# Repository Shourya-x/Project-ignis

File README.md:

# Project IGNIS — STM32G473VET6 Rocket Flight Computer & Active Fin / TVC Avionics Suite

[-03234B?style=flat-square)](IGNIS_CORE/Firmware/HAL%20STM32/IGNIS_CORE_STM32G473VET6)

> **Open-source high-power model rocket flight computer, 4-channel X-configuration active fin / TVC attitude controller, 3-stage high-current MOSFET pyro igniter system, dual-EEPROM blackbox recorder, and 433 MHz LoRa telemetry ground station.**

---

## 1. Executive Summary

**Project IGNIS** is a vertically integrated aerospace avionics and mechanical control platform engineered from custom bare-metal `STM32G473VET6` HAL firmware and 2-layer KiCad PCBs to a parametric FreeCAD airframe and a PyQt6/OpenGL ground station.

Unlike hobby flight controllers built around legacy `STM32F4` drone boards, **IGNIS-CORE** is purpose-built around the **`STM32G473VET6`** (LQFP-100, 170 MHz ARM Cortex-M4F with hardware **CORDIC** trigonometric and **FMAC** filter co-processors, 512 KB ECC Flash, 128 KB SRAM, 6 internal PGA op-amps, and 7 ultra-fast 16 ns comparators).

### Key Subsystem Capabilities

| Subsystem | Hardware Implementation | Key Specifications |
| :--- | :--- | :--- |
| **Flight Computer (`IGNIS_CORE`)** | Custom KiCad PCB + **`STM32G473VET6`** (LQFP-100) | 144 MHz PLL (`8 MHz` HSE `X1` + `32.768 kHz` LSE `X2`), 512 KB ECC Flash, 128 KB SRAM |
| **Inertial & Barometric Suite (`I2C2`)** | **`MPU-6500`** (`0x68`) + **`MS5611-01BA03`** (`0x77`) + **`HMC5883L` / `BMM150`** (`0x1E`) | $\pm 8\text{g}$ Accel ($4096\text{ LSB/g}$), $\pm 1000^\circ/\text{s}$ Gyro ($32.8\text{ LSB}/^\circ/\text{s}$), 24-bit $\Delta\Sigma$ Baro ($\text{OSR}=4096$, $\sim 10\text{ cm}$ resolution) |
| **Attitude & X-Fin / TVC Actuation** | 4× High-Speed Digital Servos on **`TIM2_CH1..4`** (`PA0–PA3`) | `100 Hz` Complementary Filter ($\alpha=0.98$) + 3-Axis PID ($K_p=1.2, K_i=0.05, K_d=0.08$) + 4-Fin X-Mixing |
| **3-Channel Pyro Igniter Stage** | 2× **`IRLZ44N`** (`PC7`, `PC8`) + 1× **`IRF520`** w/ Dual-`BC547` Level Shifter (`PC9`) | Motor Ignition (`PC7`), Stage Separation (`PC8`), Parachute Ejection (`PC9`) with `1N4007` flyback clamp diodes |
| **Telemetry & Navigation** | **`Ai-Thinker Ra-02 (SX1278)`** (`SPI1`) + **`u-blox NEO-7M`** (`USART1`) | 433 MHz LoRa long-range link (`>5 km` LOS), contiguous LQFP-100 pin routing (`Pins 90–95`) + 10 Hz GPS |
| **Dual-Tier Flight Storage** | Onboard **`24LC16B`** EEPROM (`0x50–0x57`) + **`microSD`** (`SPI2`) + **`Aux Data Logger PCB`** | Hot-start state & calibration recovery + `ATmega328P` / Dual `24LC1025` (256 KB) / `DS1337S+` RTC blackbox |
| **Diagnostics & Ground Interface** | **`WS2812B`** DMA Engine (`PB9`) + 5V NPN Buzzer (`PC6`) + **`USB-C CDC`** (`PA11/PA12`) | Zero-CPU `TIM4_CH4` + `DMA1_Channel1` 800 kHz NeoPixel driver + 100 Hz CSV telemetry stream & CLI |

---

## 2. System Architecture

```
┌─────────────────────────────────────────────────────────────────────────────────────────────────┐
│                                  PROJECT IGNIS AVIONICS STACK                                   │
├─────────────────────────────────────────────────────────────────────────────────────────────────┤
│                                                                                                 │
│  ┌───────────────────────────────────────┐        ┌──────────────────────────────────────────┐  │
│  │        I2C2 SENSOR & NVM BUS          │        │        TELEMETRY, GPS & STORAGE          │  │
│  │        (SCL = PC4, SDA = PA8)         │        │                                          │  │
│  │  • MPU-6500 6-Axis IMU       [0x68]   │        │  • SX1278 Ra-02 LoRa (SPI1: PB3–PB8)     │  │
│  │  • MS5611-01BA03 Barometer   [0x77]   │        │  • u-blox NEO-7M GPS (USART1: PA9/PA10)  │  │
│  │  • HMC5883L / BMM150 Mag     [0x1E]   │        │  • microSD Slot      (SPI2: PB12–PB15)   │  │
│  │  • 24LC16B Hot-Start EEPROM  [0x50]   │        │  • USB-C Full-Speed  (CDC: PA11/PA12)    │  │
│  └──────────────────┬────────────────────┘        └────────────────────┬─────────────────────┘  │
│                     │                                                  │                        │
│                     ▼                                                  ▼                        │
│  ┌───────────────────────────────────────────────────────────────────────────────────────────┐  │
│  │                        IGNIS-CORE FLIGHT COMPUTER (STM32G473VET6)                         │  │
│  │            170 MHz Cortex-M4F (144 MHz PLL) • CORDIC + FMAC • 512 KB ECC Flash            │  │
│  │     100 Hz Attitude Loop: Complementary Filter (α=0.98) ──► 3-Axis PID ──► X-Fin Mixer    │  │
│  └──────────────────┬──────────────────────────────────────────────────┬─────────────────────┘  │
│                     │                                                  │                        │
│                     ▼ TIM2 50Hz PWM (PA0–PA3)                          ▼ High-Current Switching │
│  ┌───────────────────────────────────────┐        ┌──────────────────────────────────────────┐  │
│  │     IGNIS-CTRL ACTUATION STAGE        │        │      3-CHANNEL PYRO & DIAGNOSTICS        │  │
│  │  • Fin 1 (45°  / Q1: +X,+Y) : PA0 (CH1)│       │  • PC7 (PYRO_MOTOR) : IRLZ44N Logic FET  │  │
│  │  • Fin 2 (135° / Q2: -X,+Y) : PA1 (CH2)│       │  • PC8 (PYRO_SEP)   : IRLZ44N Logic FET  │  │
│  │  • Fin 3 (225° / Q3: -X,-Y) : PA2 (CH3)│       │  • PC9 (PYRO_CHUTE) : 2x BC547 + IRF520  │  │
│  │  • Fin 4 (315° / Q4: +X,-Y) : PA3 (CH4)│       │  • PC6 (BUZZER)     : BC547 + 1N4007     │  │
│  │  • 2-Axis TVC Gimbal Assembly         │        │  • PB9 (WS2812B)    : TIM4_CH4 + DMA     │  │
│  └───────────────────────────────────────┘        └──────────────────────────────────────────┘  │
│                                                                                                 │
└─────────────────────────────────────────────────────────────────────────────────────────────────┘
```

---

## 3. Repository Structure

```text
Project-ignis/
├── IGNIS_CORE/
│   ├── Firmware/
│   │   ├── HAL STM32/IGNIS_CORE_STM32G473VET6/  # Primary STM32CubeMX + CMake + Modular HAL Firmware
│   │   │   ├── Core/                            # CubeMX-generated peripheral init (gpio, dma, i2c, spi, tim, usart)
│   │   │   ├── Modules/                         # 11 CubeMX-safe hardware & GNC modules:
│   │   │   │   ├── Flight/                      # 100 Hz Complementary filter, 3-axis PID & X-fin mixing
│   │   │   │   ├── IMU/                         # MPU-6500 register driver & 500-sample offset calibration
│   │   │   │   ├── Barometer/                   # MS5611 PROM C1-C6 reader & 2nd-order temp-compensated ADC
│   │   │   │   ├── Sensors/                     # I2C2 bus scanner (0x08-0x77) & HMC5883L 3-axis magnetometer
│   │   │   │   ├── Servos/                      # TIM2 4-channel 50 Hz hardware PWM (1000-2000 µs)
│   │   │   │   ├── WS2812/                      # TIM4_CH4 + DMA1_Channel1 zero-CPU NeoPixel pulse engine
│   │   │   │   ├── EEPROM/                      # 24LC16B 8-block (0x50-0x57) hot-start & calibration storage
│   │   │   │   ├── LoRa/                        # SX1278 (Ra-02) SPI1 radio driver
│   │   │   │   ├── GPS/                         # u-blox NEO-7M USART1 NMEA parser
│   │   │   │   ├── Logger/ & Storage/           # SPI2 microSD & blackbox telemetry logging
│   │   │   │   └── USB/                         # USB-C Full-Speed CDC 100 Hz CSV stream & interactive CLI
│   │   │   ├── IGNIS_CORE_STM32G473VET6.ioc     # STM32CubeMX hardware pinout & clock definition
│   │   │   ├── CMakeLists.txt                   # CMake + Ninja build definition
│   │   │   └── new_module.sh                    # Automated HAL module generator script
│   │   └── PlatFormio/                          # Legacy prototype firmware archive
│   ├── Hardware/
│   │   ├── Project_IGNIS_CORE/                  # Main Flight Computer KiCad 9/10 Schematic, PCB & STEP
│   │   ├── 3D_Models/ & Footprints.pretty/      # Custom SMD/THT footprints & 3D component models
│   │   └── Documentation/                       # Exported schematics.pdf & BOM.xlsx
│   └── Aux Hardware/Data Logger/data logger/    # Standalone ATmega328P + 2x 24LC1025 + DS1337S RTC PCB
│
├── IGNIS_CTRL/
│   └── Mechanical_Design/                       # TVC gimbal STEP/STL CAD files (thrust plate, linkages, mounts)
│
├── IGNIS_NET/
│   ├── IGNIS-NET-SIM/                           # PyQt6 + PyQtGraph + PyOpenGL Ground Station & Flight Replayer
│   ├── Firmware/                                # Ground station receiver firmware
│   └── Documentation/                           # Ground station user manual & API docs
│
├── Rocket_Assembly/
│   ├── Airframe And Parts/                      # Parametric FreeCAD (.FCStd), STEP & STL rocket body, fins, nosecone
│   ├── Avionics_Bay/                            # Modular avionics bay (.FCStd, .gltf, .stl), shock mounts & core mount
│   └── Full_Assembly/                           # Complete rocket assembly & cutaway STEP models
│
├── Documentation/                               # Comprehensive engineering & hardware documentation
│   ├── System_Overview.md                       # Architecture, G4 vs F4 trade study, control loop & power tree
│   ├── Wiring_Guide.md                          # Complete LQFP-100 pinout, Pyro MOSFET & Buzzer schematics
│   ├── Communication_Protocol.md                # USB CDC 100 Hz CSV, CLI commands & LoRa telemetry frame specs
│   ├── Calibration_Guide.md                     # IMU 500-sample bias, MS5611 PROM, Magnetometer & Servo centering
│   └── Troubleshooting.md                       # Hardware bringup, WS2812 DMA timing, I2C2 mux & PCB DRC notes
│
└── ignis-website/                               # Astro Technical Datasheet & 3D Interactive Avionics Showcase
```

---

## 4. Complete `STM32G473VET6` (LQFP-100) Pinout Matrix

| LQFP-100 Pin | GPIO Pin | Peripheral / Mode | Signal Label | Connected Hardware & Engineering Notes |
| :---: | :---: | :--- | :--- | :--- |
| **Pin 12 / 13** | `PH0 / PH1` | `RCC_OSC_IN / OUT` | `HSE_8MHZ` | `X1` 8.000 MHz HC-49US crystal $\rightarrow$ PLL $\times 36 / 2 = \mathbf{144\text{ MHz}}$ `SYSCLK` |
| **Pin 8 / 9** | `PC14 / PC15` | `RCC_OSC32_IN / OUT` | `LSE_32K` | `X2` 32.768 kHz RTC crystal |
| **Pin 30** | **`PC4`** | `I2C2_SCL` (AF4) | `I2C2_SCL` | `MPU-6500` (`0x68`), `MS5611` (`0x77`), `HMC5883L` (`0x1E`), `24LC16B` (`0x50–0x57`) |
| **Pin 69** | **`PA8`** | `I2C2_SDA` (AF4) | `I2C2_SDA` | Shared `I2C2` bus (`4.7 kΩ` pull-ups to `+3.3V`) |
| **Pin 22** | **`PA0`** | `TIM2_CH1` (AF1) | `SERVO_FIN1` | **Fin 1 (45° / Q1: +X, +Y)** 50 Hz PWM (`1000–2000 µs`, $90^\circ = 1500\,\mu\text{s}$) |
| **Pin 23** | **`PA1`** | `TIM2_CH2` (AF1) | `SERVO_FIN2` | **Fin 2 (135° / Q2: -X, +Y)** 50 Hz PWM (`1000–2000 µs`) |
| **Pin 24** | **`PA2`** | `TIM2_CH3` (AF1) | `SERVO_FIN3` | **Fin 3 (225° / Q3: -X, -Y)** 50 Hz PWM (`1000–2000 µs`) |
| **Pin 25** | **`PA3`** | `TIM2_CH4` (AF1) | `SERVO_FIN4` | **Fin 4 (315° / Q4: +X, -Y)** 50 Hz PWM (`1000–2000 µs`) |
| **Pin 90** | **`PB3`** | `SPI1_SCK` (AF5) | `LORA_SCK` | `Ai-Thinker Ra-02 (SX1278)` Clock (Consecutive LQFP row `Pins 90–95`) |
| **Pin 91** | **`PB4`** | `SPI1_MISO` (AF5) | `LORA_MISO` | `Ai-Thinker Ra-02 (SX1278)` MISO |
| **Pin 92** | **`PB5`** | `SPI1_MOSI` (AF5) | `LORA_MOSI` | `Ai-Thinker Ra-02 (SX1278)` MOSI |
| **Pin 93** | **`PB6`** | `GPIO_Output` | `LORA_RST` | `Ai-Thinker Ra-02 (SX1278)` Active-Low Reset (Default `HIGH`) |
| **Pin 94** | **`PB7`** | `GPIO_Output` | `LORA_CS` | `Ai-Thinker Ra-02 (SX1278)` Chip Select (`NSS`, Default `HIGH`) |
| **Pin 95** | **`PB8`** | `GPIO_EXTI8` | `LORA_DIO0` | `Ai-Thinker Ra-02 (SX1278)` Packet Tx/Rx Done Interrupt |
| **Pin 96** | **`PB9`** | `TIM4_CH4` + `DMA1_CH1` | `WS2812_DI` | `WS2812B` Addressable Status LED (`800 kHz`, 2 preamble + 24 data + 240 reset slots) |
| **Pin 70** | **`PA9`** | `USART1_TX` (AF7) | `GPS_RXD` | `u-blox NEO-7M` GPS Receiver (`9600` baud) |
| **Pin 71** | **`PA10`** | `USART1_RX` (AF7) | `GPS_TXD` | `u-blox NEO-7M` GPS Transmitter (`9600` baud) |
| **Pin 51** | **`PB12`** | `GPIO_Output` | `SD_CS` | `microSD` Card SPI Chip Select (Default `HIGH`) |
| **Pin 52** | **`PB13`** | `SPI2_SCK` (AF5) | `SD_SCK` | `microSD` Card SPI2 Clock |
| **Pin 53** | **`PB14`** | `SPI2_MISO` (AF5) | `SD_MISO` | `microSD` Card SPI2 MISO |
| **Pin 54** | **`PB15`** | `SPI2_MOSI` (AF5) | `SD_MOSI` | `microSD` Card SPI2 MOSI |
| **Pin 65** | **`PC6`** | `GPIO_Output` | `BUZZER` | 5V Piezo Buzzer via `BC547` NPN low-side driver + `1N4007` flyback diode |
| **Pin 66** | **`PC7`** | `GPIO_Output` | `PYRO_MOTOR` | **Pyro Channel 1 (Motor Igniter)** — Direct 3.3V logic gate drive to `IRLZ44N` |
| **Pin 67** | **`PC8`** | `GPIO_Output` | `PYRO_SEP` | **Pyro Channel 2 (Stage Separation)** — Direct 3.3V logic gate drive to `IRLZ44N` |
| **Pin 68** | **`PC9`** | `GPIO_Output` | `PYRO_CHUTE` | **Pyro Channel 3 (Parachute Ejection)** — Dual-`BC547` NPN level-shifter $\rightarrow$ `IRF520` (`V_GS = V_BAT`) |
| **Pin 72 / 73** | **`PA11 / PA12`** | `USB_DM / USB_DP` | `USB_CDC` | USB-C Full-Speed Virtual COM Port (`100 Hz` telemetry & interactive command console) |
| **Pin 76 / 79** | **`PA13 / PA14`** | `SYS_JTMS / JTCK` | `SWDIO / SWCLK` | ST-Link V2 Serial Wire Debug & Flash Programming |

---

## 5. Flight Control Loop & X-Configuration Fin Mixing

The attitude control loop in [`Flight.c`](IGNIS_CORE/Firmware/HAL%20STM32/IGNIS_CORE_STM32G473VET6/Modules/Flight/Flight.c) executes deterministically at **`100 Hz` ($\Delta t = 10\text{ ms}$)**:

1. **Inertial Attitude Estimation (Complementary Filter, $\alpha = 0.98$)**:
   $$\theta_{\text{accel}} = \text{atan2}\!\left(-a_x, \sqrt{a_y^2 + a_z^2}\right)\cdot\frac{180}{\pi}, \qquad \phi_{\text{accel}} = \text{atan2}\!\left(a_y, -a_z\right)\cdot\frac{180}{\pi}$$
   $$\theta_k = 0.98\left(\theta_{k-1} + \omega_x \Delta t\right) + 0.02\,\theta_{\text{accel}}, \qquad \phi_k = 0.98\left(\phi_{k-1} + \omega_y \Delta t\right) + 0.02\,\phi_{\text{accel}}$$

2. **3-Axis PID Attitude Controller** ($K_p = 1.20$, $K_i = 0.05$, $K_d = 0.08$, anti-windup clamped to $\pm 100^\circ$):
   - Pitch & Roll hold vertical attitude setpoint ($0.0^\circ$); Yaw damps angular rate ($\omega_z \rightarrow 0^\circ/\text{s}$).

3. **Orthogonal 4-Fin X-Configuration Aerodynamic Mixing Matrix**:
   $$\begin{bmatrix} \delta_1\ (45^\circ\text{ / Q1}) \\ \delta_2\ (135^\circ\text{ / Q2}) \\ \delta_3\ (225^\circ\text{ / Q3}) \\ \delta_4\ (315^\circ\text{ / Q4}) \end{bmatrix} = 90^\circ + \begin{bmatrix} -0.707 & +1.0 & -0.707 \\ +0.707 & +1.0 & -0.707 \\ +0.707 & +1.0 & +0.707 \\ -0.707 & +1.0 & +0.707 \end{bmatrix} \begin{bmatrix} u_{\text{pitch}} \\ u_{\text{roll}} \\ u_{\text{yaw}} \end{bmatrix}, \quad \delta_i \in [0^\circ, 180^\circ]$$

---

## 6. Quick Start — Firmware, Simulator & Website

### A. Build & Flash `IGNIS_CORE` (`STM32G473VET6`)

```bash
cd "IGNIS_CORE/Firmware/HAL STM32/IGNIS_CORE_STM32G473VET6"
cmake --preset Debug
cmake --build build/Debug -j

# Flash via ST-Link over SWD:
STM32_Programmer_CLI -c port=SWD -w build/Debug/IGNIS_CORE_STM32G473VET6.elf -v -rst
```

### B. Launch the `IGNIS-NET-SIM` Ground Station & Post-Flight Analyzer

```bash
cd IGNIS_NET/IGNIS-NET-SIM
python3 -m venv venv
source venv/bin/activate
pip install -r requirements.txt
python3 src/main.py
```

### C. Run the Technical Datasheet & 3D Avionics Website

```bash
cd ignis-website
npm install
npm run dev      # Local dev server at http://localhost:4321
npm run build    # Static bundle output into ./dist/
```

---

## 7. Engineering Documentation Index

- **[System Overview & Architecture](Documentation/System_Overview.md)** — `STM32G473VET6` vs `STM32F4` trade study, power regulation architecture, state machine, and Aux Blackbox Data Logger design.
- **[Hardware Wiring & Circuit Guide](Documentation/Wiring_Guide.md)** — Pin-by-pin LQFP-100 connections, `IRLZ44N` & `2× BC547 + IRF520` Pyro Igniter schematics, `5V` Buzzer driver, and `24LC16B` wiring.
- **[Communication & Telemetry Protocol](Documentation/Communication_Protocol.md)** — `100 Hz` USB CDC CSV format, single-character CLI commands (`A`, `D`, `C`, `S`), and `SX1278` LoRa telemetry frames.
- **[Sensor & Actuator Calibration Guide](Documentation/Calibration_Guide.md)** — 500-sample IMU bias calibration, `MS5611` 2nd-order PROM compensation, `HMC5883L` heading calibration, and fin trim alignment.
- **[Hardware Bringup & Troubleshooting](Documentation/Troubleshooting.md)** — `WS2812B` `TIM4_CH4` DMA waveform verification, `I2C2` `PC4`/`PA8` pin mux notes, and `IGNIS_CORE` PCB rev-1 ERC/DRC audit checklist.

---

## 8. License

- **Firmware, Ground Station Software & Documentation**: Licensed under the **MIT License**.
- **Hardware Schematics, PCB Layouts & Mechanical CAD**: Released under the **CERN Open Hardware Licence v2 — Permissive (CERN-OHL-P v2)**.

---
*Designed and engineered by **Shourya Pandey**.*

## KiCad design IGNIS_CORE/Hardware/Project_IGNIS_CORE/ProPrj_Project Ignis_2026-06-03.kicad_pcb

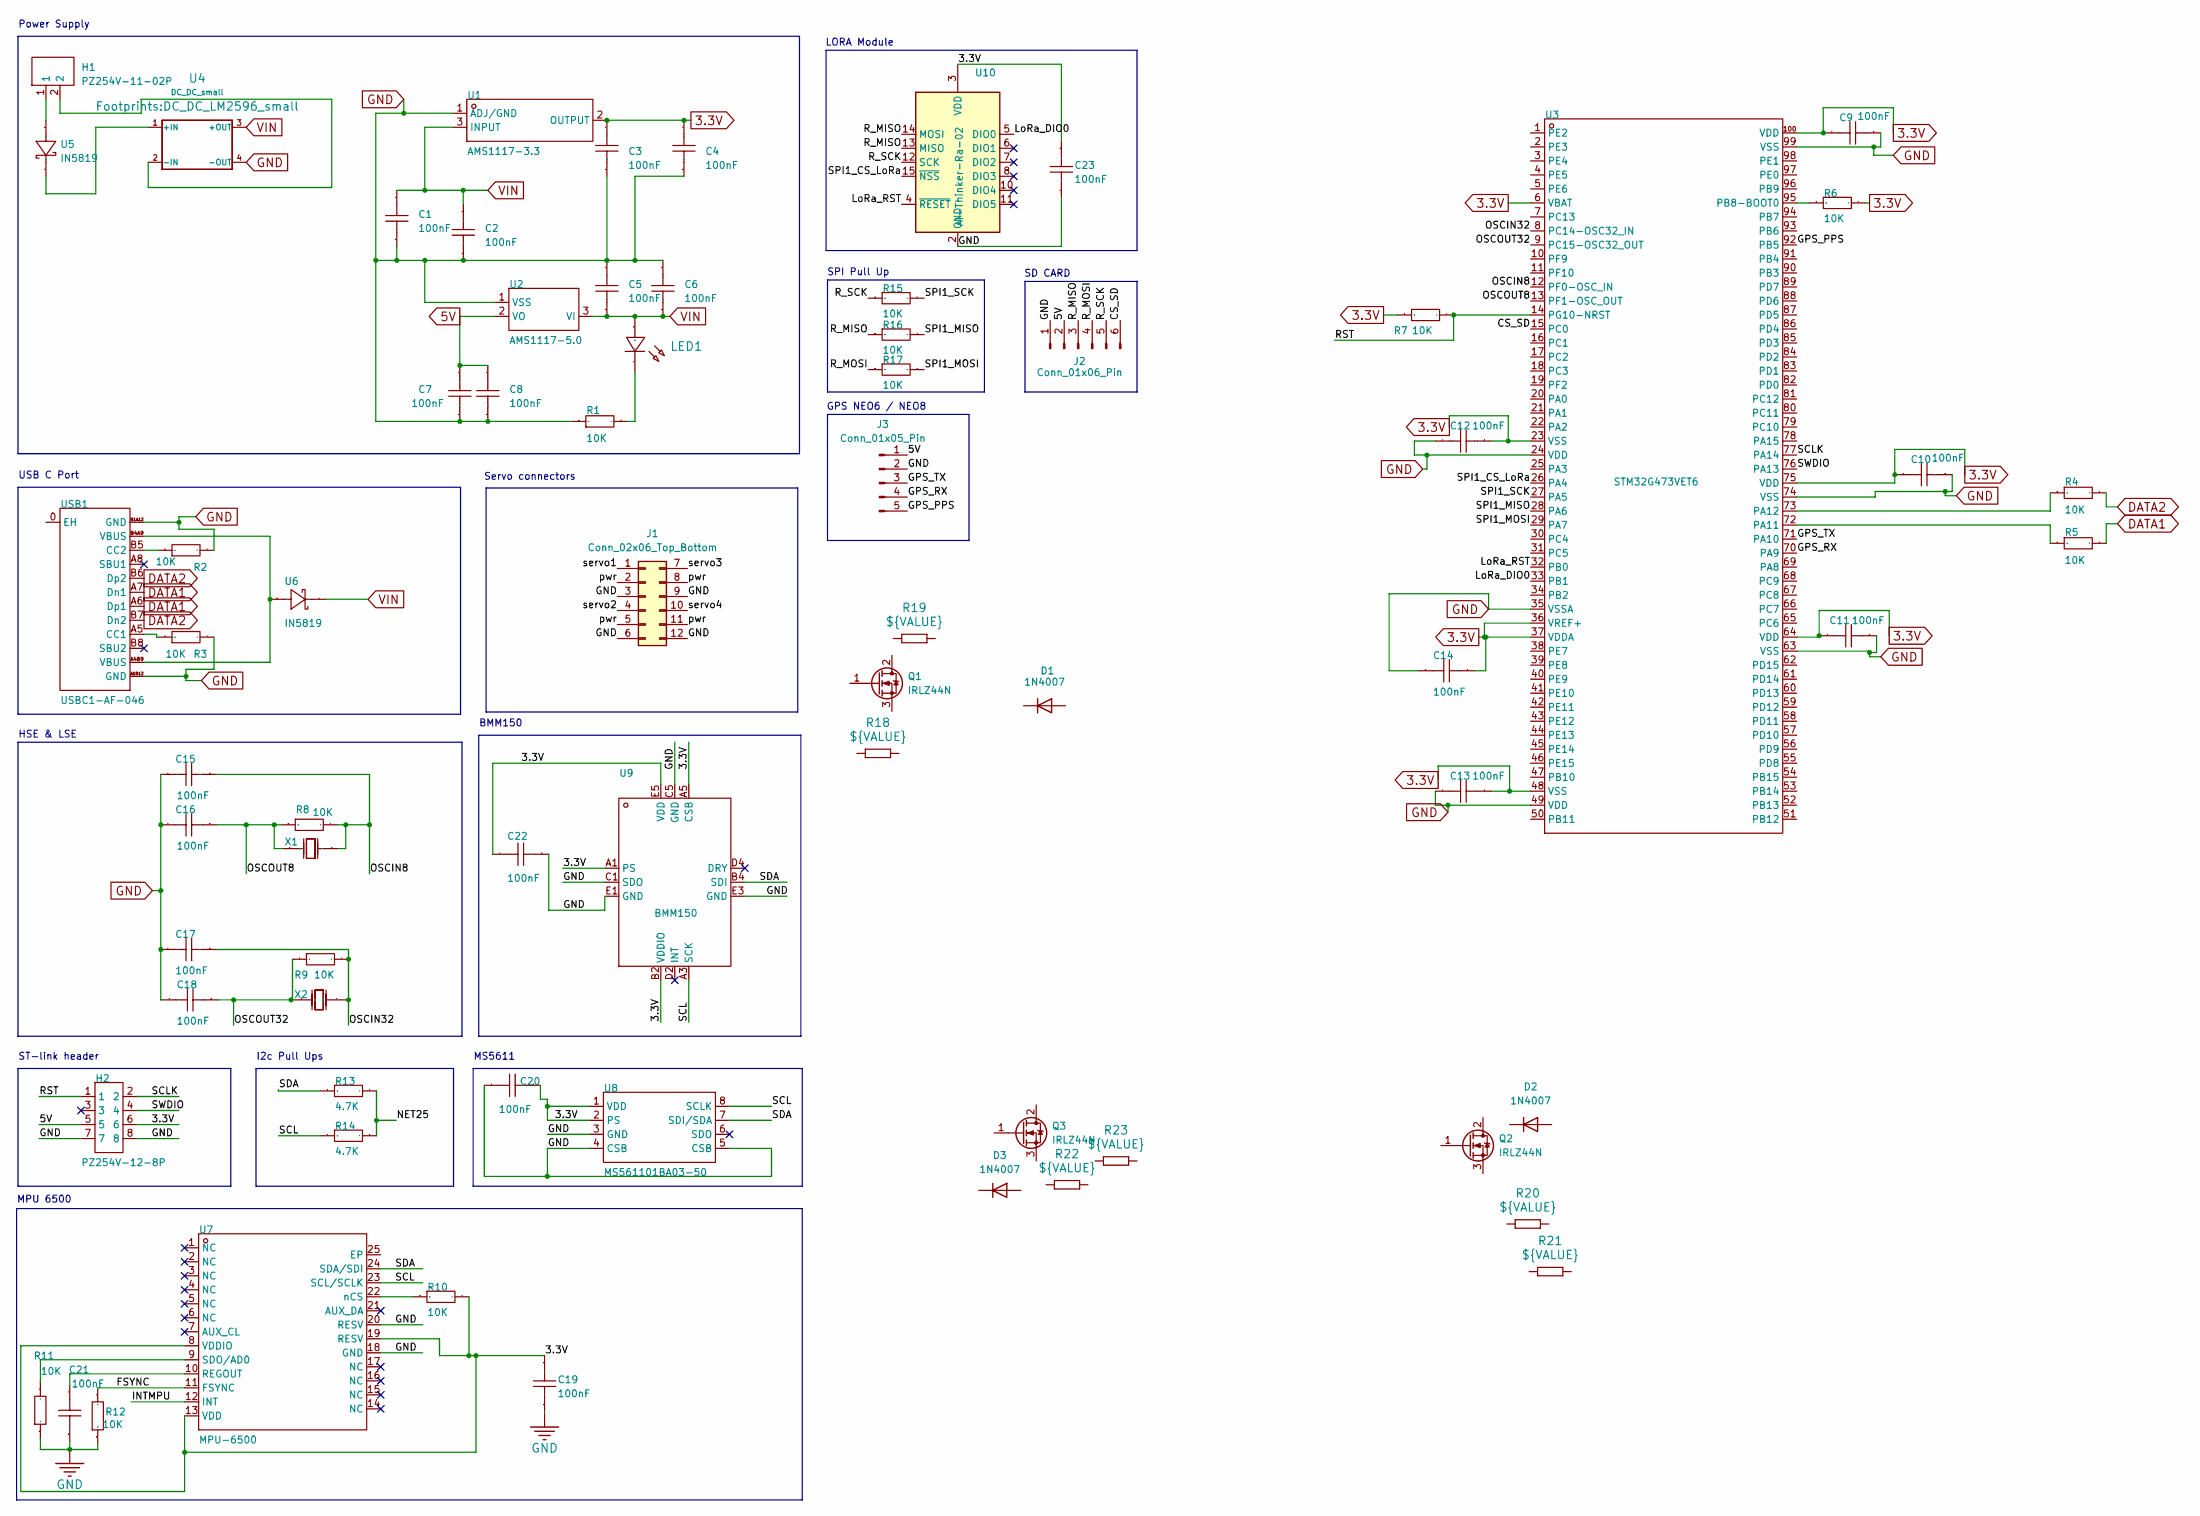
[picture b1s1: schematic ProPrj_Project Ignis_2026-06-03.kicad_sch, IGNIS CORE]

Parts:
C1, C2, C3, C4, C5, C6, C7, C8, C9, C10, C11, C12, C13, C14, C15, C16, C17, C18, C19, C20, C21, C22, C23: 100nF; C_0805_2012Metric
D1, D2, D3: 1N4007; D_DO-41_SOD81_P10.16mm_Horizontal
H1: PZ254V-11-02P; PinHeader_1x02_P2.00mm_Vertical; Manufacturer Part PZ254V-11-02P; LCSC Part Name 1x2P 间距:2.54mm 方针 直插
H2: PZ254V-12-8P; PinHeader_2x04_P2.00mm_Vertical; Manufacturer Part PZ254V-12-8P; LCSC Part Name 2x4P 间距:2.54mm 方针 直插
J1: Conn_02x06_Top_Bottom; PinHeader_2x06_P2.00mm_Vertical
J2: Conn_01x06_Pin; PinHeader_1x06_P2.00mm_Vertical
J3: Conn_01x05_Pin; PinHeader_1x05_P2.00mm_Vertical
LED1: LED_0805_2012Metric
Q1, Q2, Q3: IRLZ44N; TO-220-3_Vertical
R1, R2, R3, R4, R5, R6, R7, R8, R9, R10, R11, R12, R15, R16, R17: 10K; R_0805_2012Metric
R13, R14: 4.7K; R_0805_2012Metric
R18, R19, R20, R21, R22, R23: ${VALUE}; R_0805_2012Metric
U1: AMS1117-3.3; TO-252-2_L6.6-W5.6-P2.3-LS9.7; Manufacturer Part AMS1117-3.3; LCSC Part Name AMS1117-3.3
U2: AMS1117-5.0; TO-252-2_L6.6-W5.6-P2.3-LS9.7; Manufacturer Part AMS1117-5.0; LCSC Part Name AMS1117-5.0
U3: STM32G473VET6; LQFP-100_L14.0-W14.0-P0.50-LS16.0-BL; Manufacturer Part STM32G473VET6; LCSC Part Name 带DSP和FPU的170MHz主流ARM Cortex-M4 MCU，具有51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
U4: DC_DC_small; DC_DC_LM2596_small
U5, U6: IN5819; DO-41_BD2.4-L4.7-P8.70-D0.8-FD; Manufacturer Part IN5819; LCSC Part Name IN5819
U7: MPU-6500; QFN-24_L3.0-W3.0-P0.40-BL-EP; Manufacturer Part MPU-6500; LCSC Part Name MPU-6500
U8: MS561101BA03-50; SENSORS-SMD_MS5611-01BA03; Manufacturer Part MS561101BA03-50; LCSC Part Name 气压传感器，带不锈钢帽
U9: BMM150; WLCSP-12_L1.6-W1.6_BMM150; Manufacturer Part BMM150; LCSC Part Name 三轴地磁式传感器 停产
U10: Ai-Thinker-Ra-02; Ai-Thinker-Ra-01-LoRa
USB1: USBC1-AF-046; TE_2340901-1; Manufacturer Part USBC1-AF-046; LCSC Part Name Type-C 母 沉板
X1: 8MHz; HC-49US_L11.5-W4.5-P4.88; Manufacturer Part 6BS08000F20UCG; LCSC Part Name 8MHz ±20ppm 20pF
X2: 32.768kHz; ABS0532768KHZ6T; Manufacturer Part 9H03200028; LCSC Part Name 32.768kHz ±20ppm 7pF

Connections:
3.3V: C3.2, C4.2, C9.2, C10.2, C11.2, C12.1, C13.1, C14.1, C19.1, C20.1, C22.2, C23.1, H2.6, R6.2, R7.1, R10.2, U1.2 (OUTPUT), U3.6 (VBAT), U3.23 (VSS), U3.36 (VREF+), U3.37 (VDDA), U3.48 (VSS), U3.64 (VDD), U3.75 (VDD), U3.100 (VDD), U7.8 (VDDIO), U7.13 (VDD), U7.19 (RESV), U8.1 (VDD), U8.2 (PS), U9.A1 (PS), U9.A5 (CSB), U9.B2 (VDDIO), U9.E5 (VDD), U10.3 (VDD)
5V: C7.2, C8.2, H2.5, J2.2, J3.1, U2.2 (VO)
/CS_SD: J2.6, U3.15 (PC0)
/FSYNC: R12.2, U7.11 (FSYNC)
/GPS_PPS: J3.5, U3.92 (PB5)
/GPS_RX: J3.4, U3.70 (PA9)
/GPS_TX: J3.3, U3.71 (PA10)
/INTMPU: U7.12 (INT)
/LoRa_DIO0: U3.33 (PB1), U10.5 (DIO0)
/LoRa_RST: U3.32 (PB0), U10.4 (~RESET)
/NET25: R13.2, R14.2
/OSCIN8: C15.1, R8.2, U3.12 (PF0-OSC_IN), X1.2 (OSC2)
/OSCIN32: C17.1, R9.2, U3.8 (PC14-OSC32_IN), X2.2 (OSC2)
/OSCOUT8: C16.1, R8.1, U3.13 (PF1-OSC_OUT), X1.1 (OSC1)
/OSCOUT32: C18.1, R9.1, U3.9 (PC15-OSC32_OUT), X2.1 (OSC1)
/RST: H2.1, R7.2, U3.14 (PG10-NRST)
/R_MISO: J2.3, R16.1, U10.13 (MISO), U10.14 (MOSI)
/R_MOSI: J2.4, R17.1
/R_SCK: J2.5, R15.1, U10.12 (SCK)
/SCL: R14.1, U7.23 (SCL/SCLK), U8.8 (SCLK), U9.A3 (SCK)
/SCLK: H2.2, U3.77 (PA14)
/SDA: R13.1, U7.24 (SDA/SDI), U8.7 (SDI/SDA), U9.B4 (SDI)
/SPI1_CS_LoRa: U3.26 (PA4), U10.15 (~NSS)
/SPI1_MISO: R16.2, U3.28 (PA6)
/SPI1_MOSI: R17.2, U3.29 (PA7)
/SPI1_SCK: R15.2, U3.27 (PA5)
/SWDIO: H2.4, U3.76 (PA13)
/pwr: J1.2, J1.5, J1.8, J1.11
/servo1: J1.1
/servo2: J1.4
/servo3: J1.7
/servo4: J1.10
DATA1: R5.2, USB1.A6 (Dp1), USB1.A7 (Dn1)
DATA2: R4.2, USB1.B6 (Dp2), USB1.B7 (Dn2)
GND: C1.1, C2.2, C3.1, C4.1, C5.2, C6.2, C7.1, C8.1, C9.1, C10.1, C11.1, C12.2, C13.2, C14.2, C15.2, C16.2, C17.2, C18.2, C19.2, C20.2, C21.1, C22.1, C23.2, H2.7, H2.8, J1.3, J1.6, J1.9, J1.12, J2.1, J3.2, R1.1, R2.2, R3.2, R11.1, R12.1, U1.1 (ADJ/GND), U2.1 (VSS), U3.24 (VDD), U3.35 (VSSA), U3.49 (VDD), U3.63 (VSS), U3.74 (VSS), U3.99 (VSS), U4.4 (-OUT), U7.18 (GND), U7.20 (RESV), U8.3 (GND), U8.4 (CSB), U8.5 (CSB), U9.C1 (SDO), U9.C5 (GND), U9.E1 (GND), U9.E3 (GND), U10.1 (GND), U10.2 (GND), U10.9 (GND), U10.16 (GND), USB1.A1B12 (GND), USB1.B1A12 (GND)
unnamed: LED1.2 (C), R1.2
unnamed: R5.1, U3.72 (PA11)
unnamed: R4.1, U3.73 (PA12)
unnamed: R6.1, U3.95 (PB8-BOOT0)
unnamed: U4.1 (+IN), U5.2 (K)
unnamed: H1.2, U4.2 (-IN)
unnamed: H1.1, U5.1 (A)
unnamed: U6.1 (A), USB1.A4B9 (VBUS), USB1.B4A9 (VBUS)
unnamed: C21.2, U7.10 (REGOUT)
unnamed: R11.2, U7.9 (SDO/AD0)
unnamed: R10.1, U7.22 (nCS)
unnamed: R3.1, USB1.A5 (CC1)
unnamed: R2.1, USB1.B5 (CC2)
VIN: C1.2, C2.1, C5.1, C6.1, LED1.1 (A), U1.3 (INPUT), U2.3 (VI), U4.3 (+OUT), U6.2 (K)

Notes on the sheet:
MPU 6500
HSE & LSE
GPS NEO6 / NEO8
SPI Pull Up
SD CARD
LORA Module
I2c Pull Ups
USB C Port
MS5611
BMM150
Power Supply
Servo connectors
ST-link header

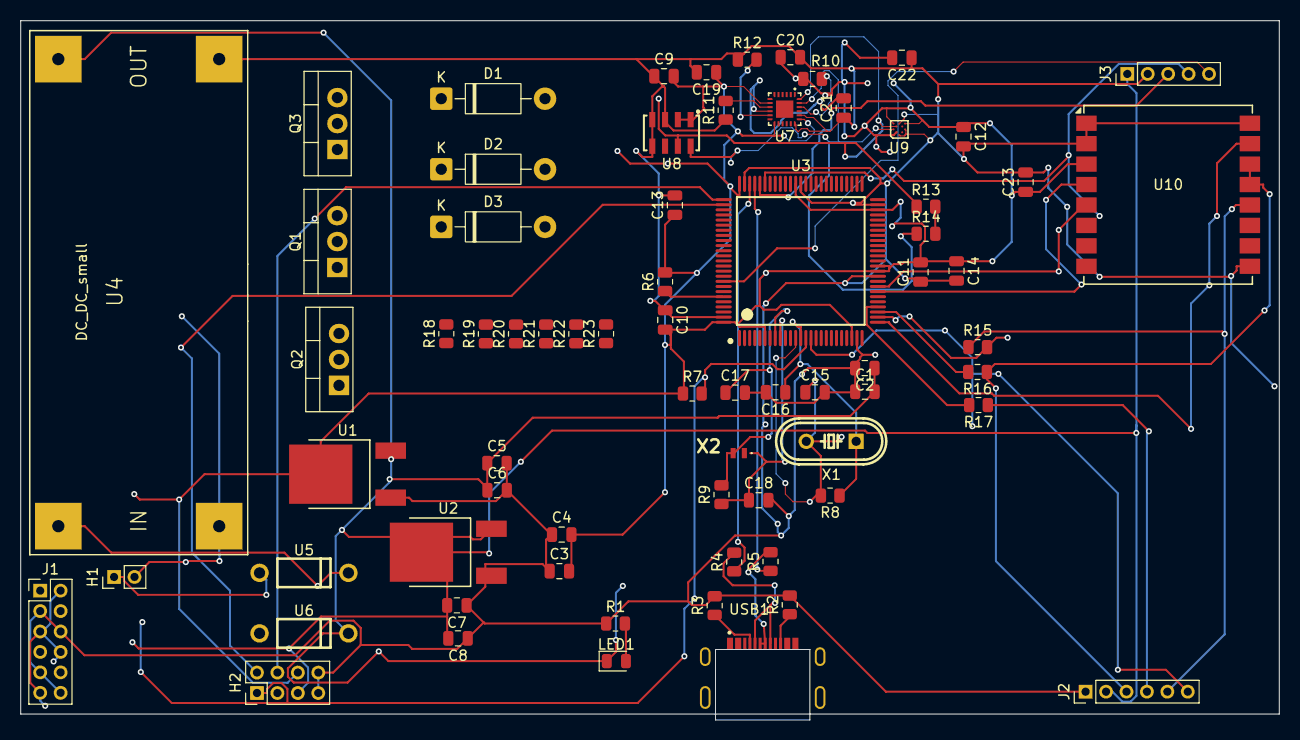
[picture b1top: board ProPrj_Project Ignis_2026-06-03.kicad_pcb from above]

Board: 2 copper layers, 123.2 x 68.4 mm, 71 parts (0 on the bottom side), 43 nets.

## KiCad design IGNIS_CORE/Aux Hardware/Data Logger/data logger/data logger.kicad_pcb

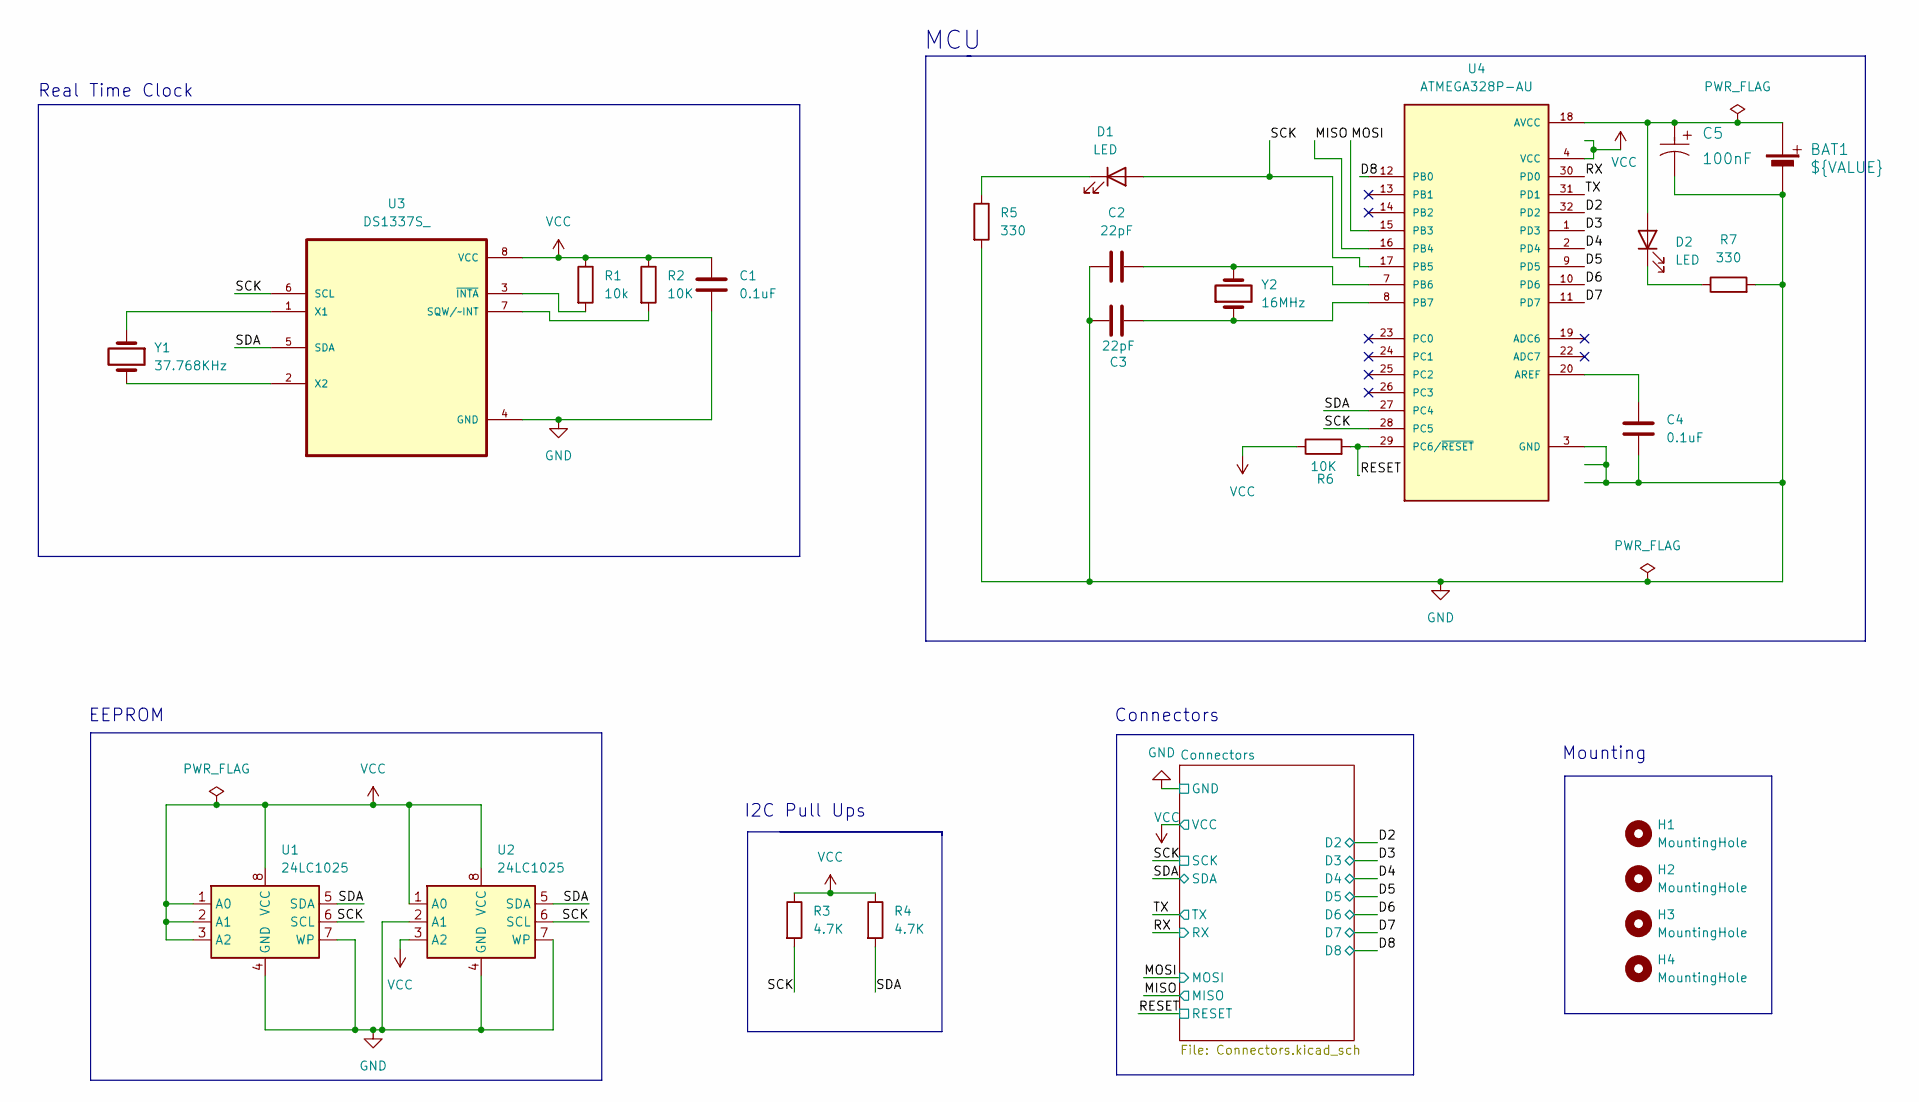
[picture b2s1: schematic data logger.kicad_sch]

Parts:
BAT1: ${VALUE}; PinHeader_1x02_P2.54mm_Vertical
C1, C4: 0.1uF; C_0805_2012Metric
C2, C3: 22pF; C_0805_2012Metric
C5: 100nF; C_0805_2012Metric
D1, D2: LED; LED_0805_2012Metric_Pad1.15x1.40mm_HandSolder
H1, H2, H3, H4: MountingHole; MountingHole_2.2mm_M2
R1: 10k; R_0805_2012Metric
R2, R6: 10K; R_0805_2012Metric
R3, R4: 4.7K; R_0805_2012Metric
R5, R7: 330; R_0805_2012Metric
U1, U2: 24LC1025; SOIC-8_5.3x5.3mm_P1.27mm
U3: DS1337S_; SOIC127P600X175-8N
U4: ATMEGA328P-AU; QFP80P900X900X120-32N; PARTREV 8271A
Y1: 37.768KHz; Crystal_SMD_5032-2Pin_5.0x3.2mm_HandSoldering
Y2: 16MHz; Crystal_SMD_5032-2Pin_5.0x3.2mm_HandSoldering

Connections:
/D2: U4.32 (PD2); also elsewhere on the board
/D3: U4.1 (PD3); also elsewhere on the board
/D4: U4.2 (PD4); also elsewhere on the board
/D5: U4.9 (PD5); also elsewhere on the board
/D6: U4.10 (PD6); also elsewhere on the board
/D7: U4.11 (PD7); also elsewhere on the board
/D8: U4.12 (PB0); also elsewhere on the board
/MISO: U4.16 (PB4); also elsewhere on the board
/MOSI: U4.15 (PB3); also elsewhere on the board
/RESET: R6.2, U4.29 (PC6/~RESET); also elsewhere on the board
/RX: U4.30 (PD0); also elsewhere on the board
/SCK: D1.2 (A), R3.2, U1.6 (SCL), U2.6 (SCL), U3.6 (SCL), U4.17 (PB5), U4.28 (PC5); also elsewhere on the board
/SDA: R4.2, U1.5 (SDA), U2.5 (SDA), U3.5 (SDA), U4.27 (PC4); also elsewhere on the board
/TX: U4.31 (PD1); also elsewhere on the board
GND: BAT1.2 (MINUS), C1.2, C2.1, C3.1, C4.2, C5.2, R5.2, R7.2, U1.4 (GND), U1.7 (WP), U2.2 (A1), U2.4 (GND), U2.7 (WP), U3.4 (GND), U4.3 (GND), U4.5 (GND), U4.21 (GND); also elsewhere on the board
unnamed: BAT1.1 (PLUS), C5.1, D2.2 (A), U4.18 (AVCC)
unnamed: D1.1 (K), R5.1
unnamed: D2.1 (K), R7.1
unnamed: R2.2, U3.7 (SQW/~INT)
unnamed: U3.1 (X1), Y1.1
unnamed: U3.2 (X2), Y1.2
unnamed: R1.2, U3.3 (~INTA)
unnamed: C4.1, U4.20 (AREF)
unnamed: C2.2, U4.7 (PB6), Y2.2
unnamed: C3.2, U4.8 (PB7), Y2.1
VCC: C1.1, R1.1, R2.1, R3.1, R4.1, R6.1, U1.1 (A0), U1.2 (A1), U1.3 (A2), U1.8 (VCC), U2.1 (A0), U2.3 (A2), U2.8 (VCC), U3.8 (VCC), U4.4 (VCC), U4.6 (VCC); also elsewhere on the board

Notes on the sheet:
Real Time Clock
EEPROM
MCU
Mounting
Connectors
I2C Pull Ups

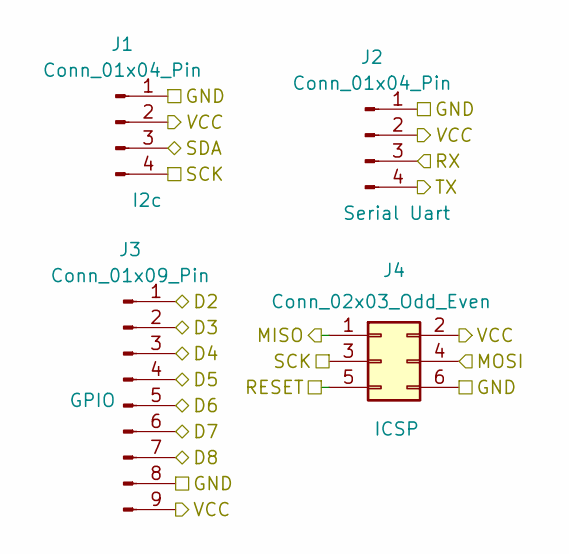
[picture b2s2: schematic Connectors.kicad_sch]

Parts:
J1, J2: Conn_01x04_Pin; PinHeader_1x04_P2.54mm_Vertical
J3: Conn_01x09_Pin; PinHeader_1x09_P2.54mm_Vertical
J4: Conn_02x03_Odd_Even; PinHeader_2x03_P2.54mm_Vertical

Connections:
/D2: J3.1; also elsewhere on the board
/D3: J3.2; also elsewhere on the board
/D4: J3.3; also elsewhere on the board
/D5: J3.4; also elsewhere on the board
/D6: J3.5; also elsewhere on the board
/D7: J3.6; also elsewhere on the board
/D8: J3.7; also elsewhere on the board
/MISO: J4.1; also elsewhere on the board
/MOSI: J4.4; also elsewhere on the board
/RESET: J4.5; also elsewhere on the board
/RX: J2.3; also elsewhere on the board
/SCK: J1.4, J4.3; also elsewhere on the board
/SDA: J1.3; also elsewhere on the board
/TX: J2.4; also elsewhere on the board
GND: J1.1, J2.1, J3.8, J4.6; also elsewhere on the board
VCC: J1.2, J2.2, J3.9, J4.2; also elsewhere on the board

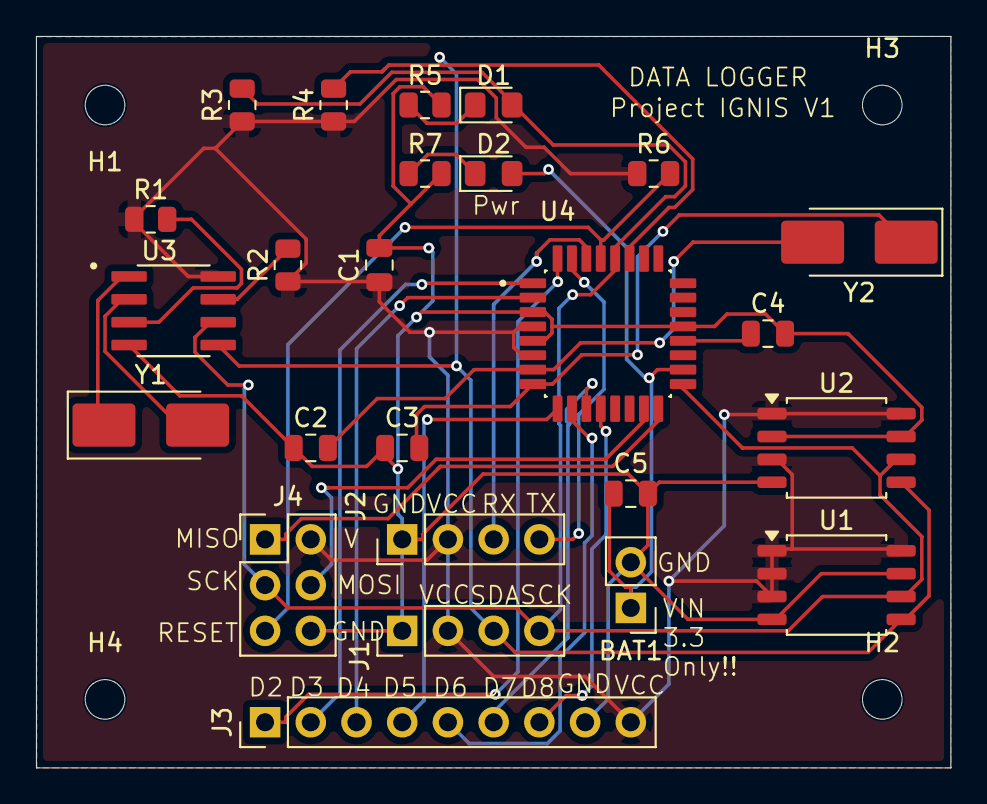
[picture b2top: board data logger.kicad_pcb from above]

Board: 2 copper layers, 50.8 x 40.6 mm, 29 parts (0 on the bottom side), 26 nets.

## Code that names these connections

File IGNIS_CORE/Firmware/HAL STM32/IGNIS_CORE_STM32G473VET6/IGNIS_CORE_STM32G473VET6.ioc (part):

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Mcu.Name=STM32G473V(B-C-E)Tx
Mcu.Package=LQFP100
Mcu.UserName=STM32G473VETx
PA0.Signal=S_TIM2_CH1
PA1.Signal=S_TIM2_CH2
PA10.Mode=Asynchronous
PA10.Signal=USART1_RX
PA11.Mode=Device
PA11.Signal=USB_DM
PA12.Mode=Device
PA12.Signal=USB_DP
PA13.Signal=SYS_JTMS-SWDIO
PA14.Signal=SYS_JTCK-SWCLK
PA2.Signal=S_TIM2_CH3
PA3.Signal=S_TIM2_CH4
PA8.GPIOParameters=GPIO_PuPd
PA8.GPIO_PuPd=GPIO_PULLUP
PA8.Mode=I2C
PA8.Signal=I2C2_SDA
PA9.Mode=Asynchronous
PA9.Signal=USART1_TX
PB12.GPIOParameters=PinState,GPIO_Label
PB12.GPIO_Label=SD_CS
PB12.PinState=GPIO_PIN_SET
PB12.Signal=GPIO_Output
PB13.Mode=Full_Duplex_Master
PB13.Signal=SPI2_SCK
PB14.Mode=Full_Duplex_Master
PB14.Signal=SPI2_MISO
PB15.Mode=Full_Duplex_Master
PB15.Signal=SPI2_MOSI
PB3.Mode=Full_Duplex_Master
PB3.Signal=SPI1_SCK
PB4.Mode=Full_Duplex_Master
PB4.Signal=SPI1_MISO
PB5.Mode=Full_Duplex_Master
PB5.Signal=SPI1_MOSI
PB6.GPIOParameters=PinState,GPIO_Label
PB6.GPIO_Label=LORA_RST
PB6.PinState=GPIO_PIN_SET
PB6.Signal=GPIO_Output
PB7.GPIOParameters=PinState,GPIO_Label
PB7.GPIO_Label=LORA_CS
PB7.PinState=GPIO_PIN_SET
PB7.Signal=GPIO_Output
PB8-BOOT0.GPIOParameters=GPIO_PuPd,GPIO_Label
PB8-BOOT0.GPIO_Label=LORA_DIO0
PB8-BOOT0.GPIO_PuPd=GPIO_PULLDOWN
PB8-BOOT0.Signal=GPXTI8
PB9.Signal=S_TIM4_CH4
PC4.GPIOParameters=GPIO_PuPd
PC4.GPIO_PuPd=GPIO_PULLUP
PC4.Mode=I2C
PC4.Signal=I2C2_SCL
PC6.GPIOParameters=PinState,GPIO_PuPd,GPIO_Label
PC6.GPIO_Label=BUZZER
PC6.GPIO_PuPd=GPIO_PULLDOWN
PC6.PinState=GPIO_PIN_RESET
PC6.Signal=GPIO_Output
PC7.GPIOParameters=PinState,GPIO_PuPd,GPIO_Label
PC7.GPIO_Label=PYRO_MOTOR
PC7.GPIO_PuPd=GPIO_PULLDOWN
PC7.PinState=GPIO_PIN_RESET
PC7.Signal=GPIO_Output
PC8.GPIOParameters=PinState,GPIO_PuPd,GPIO_Label
PC8.GPIO_Label=PYRO_SEP
PC8.GPIO_PuPd=GPIO_PULLDOWN
PC8.PinState=GPIO_PIN_RESET
PC8.Signal=GPIO_Output
PC9.GPIOParameters=PinState,GPIO_PuPd,GPIO_Label
PC9.GPIO_Label=PYRO_CHUTE
PC9.GPIO_PuPd=GPIO_PULLDOWN
PC9.PinState=GPIO_PIN_RESET
PC9.Signal=GPIO_Output
PF0-OSC_IN.Mode=HSE-External-Oscillator
PF0-OSC_IN.Signal=RCC_OSC_IN
PF1-OSC_OUT.Mode=HSE-External-Oscillator
PF1-OSC_OUT.Signal=RCC_OSC_OUT
RCC.HSE_VALUE=8000000
RCC.SYSCLKFreq_VALUE=144000000
RCC.SYSCLKSource=RCC_SYSCLKSOURCE_PLLCLK
board=custom

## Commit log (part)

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2026-04-13 Complete IGNIS project with website
2026-04-13 Trigger redeploy for custom domain
2026-04-22 Update README.md
    This is the more descriptive version of readme.md
2026-04-22 Delete Website directory
    of no use
2026-04-22 Create Code of Conduct.md
    code of conduct for the project established
2026-04-25 added the full rocket assembly model
2026-04-25 Added the airframe Files
2026-04-25 Fixed Typo's
2026-05-06 Add files via upload
    This motor nozzel is made in FREECAD software. I can support 35mm radius of rocket motor. This nozzel should be made by steel.
2026-05-20 just routine dev , i forgot what i was doing, but i think i was trying to add the stm32g473vet6 project to the repository, so here we go
2026-05-21 just routine
2026-06-09 Updates New Pcb, New Firmware Changes, New Mechanical Parts and Cleared And Added Documentation

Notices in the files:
README.md:
License: MIT / CERN-OHL
